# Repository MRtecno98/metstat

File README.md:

# Metstat
A fully autonomous, unattended, solar-powered, IoT weather probe with mesh networking capabilities.

<br>

## Hardware stack
| Component  | Part | Notes |
| - | - | - |
| MCU | `STM32L4A6AG` | Low power MCU with small package size, decent connectivity and hardware acceleration for crypto algorithms |
| Power Supply  | `SPV1050` | Integrated energy harvester with Max Power Point Tracking. Managing intake from solar panels and LiPo storage |
| `TODO` | `TODO` | `TODO` |

## Firmware stack
Written in C++, runs on the standard STM32 [HAL](https://www.st.com/resource/en/user_manual/um1725-description-of-stm32f4-hal-and-lowlayer-drivers-stmicroelectronics.pdf) 
using [CubeMX](https://www.st.com/en/development-tools/stm32cubemx.html) (standard runtime for STM32s).

## Technical description
`todo`

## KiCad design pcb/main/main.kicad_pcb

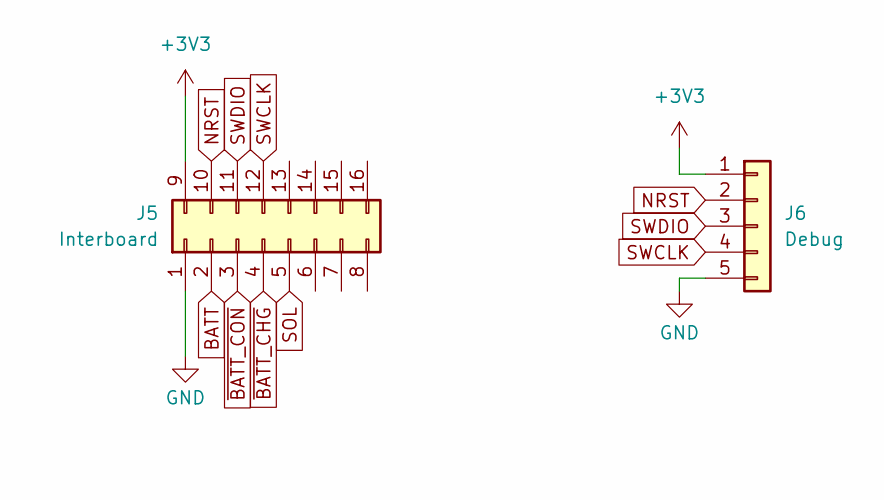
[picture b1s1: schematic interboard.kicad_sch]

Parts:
J5: Interboard; PinSocket_2x08_P2.54mm_Vertical
J6: Debug; PinHeader_1x05_P2.54mm_Horizontal

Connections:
+3V3: J5.9, J6.1; also elsewhere on the board
BATT: J5.2; also elsewhere on the board
GND: J5.1, J6.5; also elsewhere on the board
NRST: J5.10, J6.2; also elsewhere on the board
SOL: J5.5; also elsewhere on the board
SWCLK: J5.12, J6.4; also elsewhere on the board
SWDIO: J5.11, J6.3; also elsewhere on the board
~BATT_CHG: J5.4; also elsewhere on the board
~BATT_CON: J5.3; also elsewhere on the board

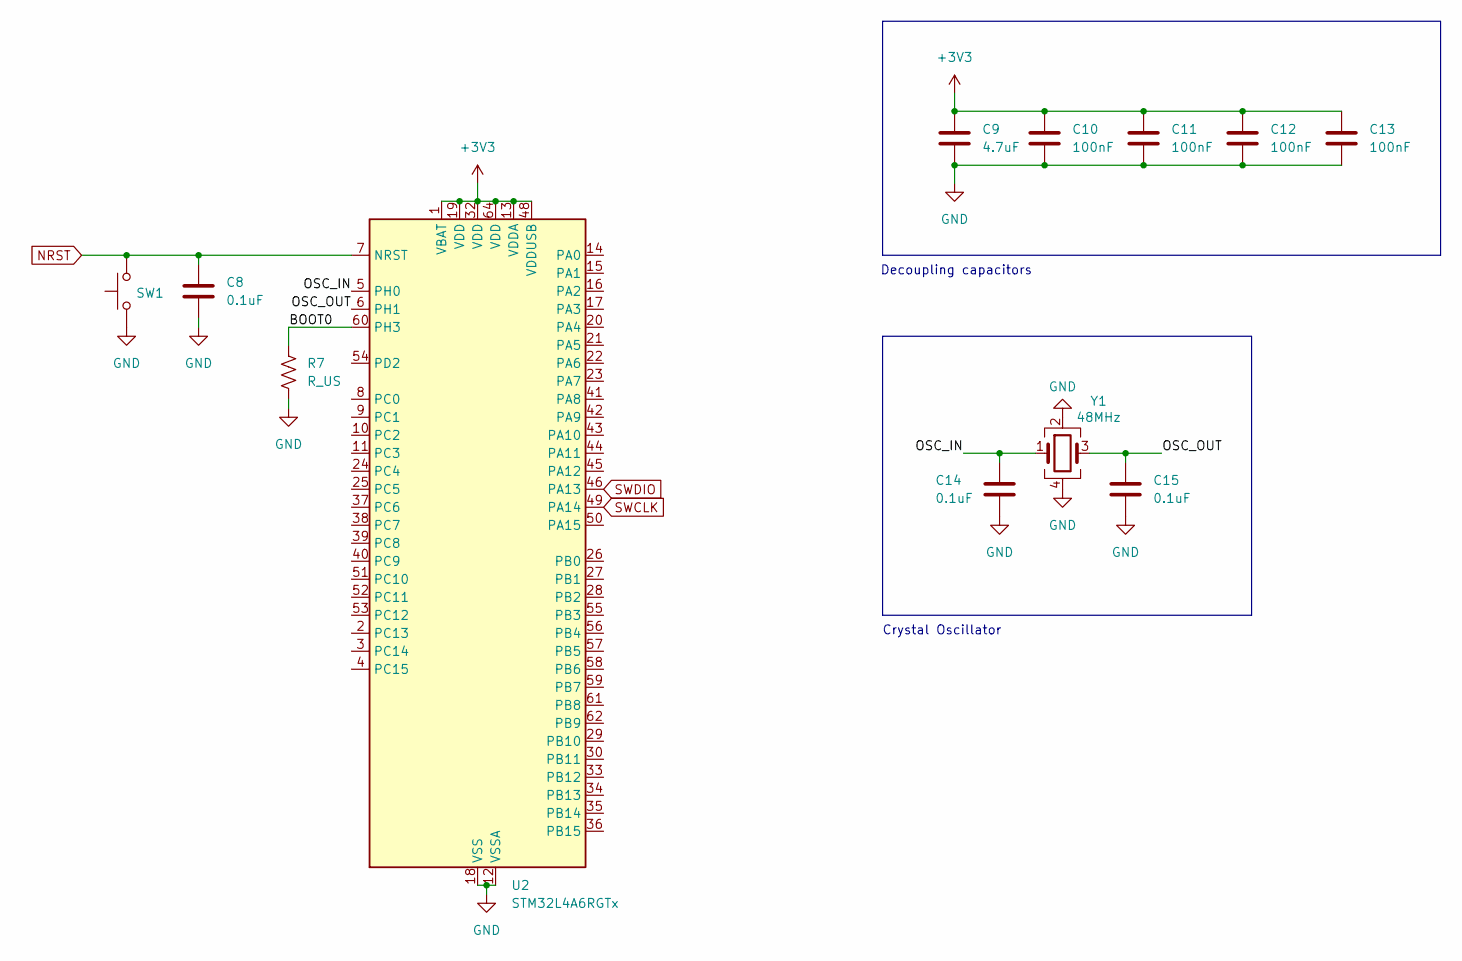
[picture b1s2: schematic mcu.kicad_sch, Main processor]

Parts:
C8, C14, C15: 0.1uF; C_0603_1608Metric_Pad1.08x0.95mm_HandSolder
C9: 4.7uF; C_0603_1608Metric_Pad1.08x0.95mm_HandSolder
C10, C11, C12, C13: 100nF; C_0603_1608Metric_Pad1.08x0.95mm_HandSolder
R7: R_US; R_0603_1608Metric_Pad0.98x0.95mm_HandSolder
SW1: SW_Push; SW_PUSH_6mm_H5mm
U2: STM32L4A6RGTx; LQFP-64_10x10mm_P0.5mm
Y1: 48MHz; Crystal_SMD_2016-4Pin_2.0x1.6mm

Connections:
+3V3: C9.1, C10.1, C11.1, C12.1, C13.1, U2.1 (VBAT), U2.13 (VDDA), U2.19 (VDD), U2.32 (VDD), U2.48 (VDDUSB), U2.64 (VDD); also elsewhere on the board
/MCU/BOOT0: R7.1, U2.60 (PH3)
/MCU/OSC_IN: C14.1, U2.5 (PH0), Y1.1
/MCU/OSC_OUT: C15.1, U2.6 (PH1), Y1.3
GND: C8.2, C9.2, C10.2, C11.2, C12.2, C13.2, C14.2, C15.2, R7.2, SW1.1, U2.12 (VSSA), U2.18 (VSS), U2.31 (VSS), U2.47 (VSS), U2.63 (VSS), Y1.2, Y1.4; also elsewhere on the board
NRST: C8.1, SW1.2, U2.7 (NRST); also elsewhere on the board
SWCLK: U2.49 (PA14); also elsewhere on the board
SWDIO: U2.46 (PA13); also elsewhere on the board

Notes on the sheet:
Crystal Oscillator
Decoupling capacitors

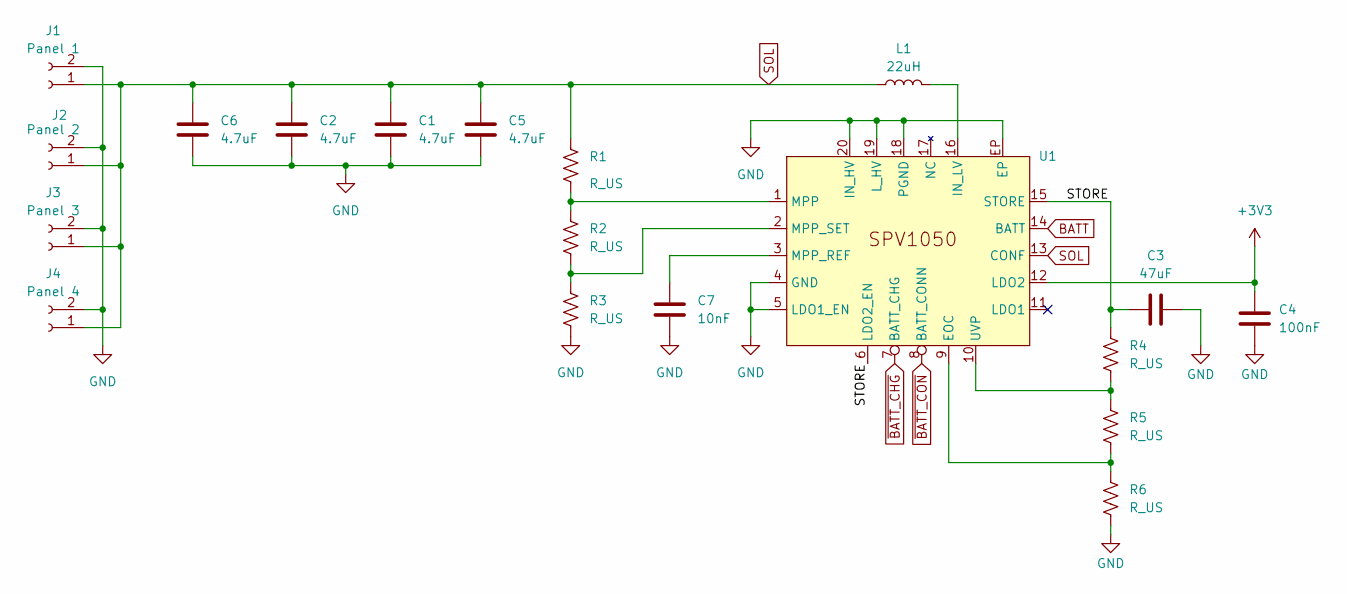
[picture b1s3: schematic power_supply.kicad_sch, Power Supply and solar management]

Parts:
C1, C2, C5, C6: 4.7uF; C_0603_1608Metric_Pad1.08x0.95mm_HandSolder
C3: 47uF; C_0603_1608Metric_Pad1.08x0.95mm_HandSolder
C4: 100nF; C_0603_1608Metric_Pad1.08x0.95mm_HandSolder
C7: 10nF; C_0603_1608Metric_Pad1.08x0.95mm_HandSolder
J1: Panel 1; Molex_PicoBlade_53261-0271_1x02-1MP_P1.25mm_Horizontal
J2: Panel 2; Molex_PicoBlade_53261-0271_1x02-1MP_P1.25mm_Horizontal
J3: Panel 3; Molex_PicoBlade_53261-0271_1x02-1MP_P1.25mm_Horizontal
J4: Panel 4; Molex_PicoBlade_53261-0271_1x02-1MP_P1.25mm_Horizontal
L1: 22uH; L_0603_1608Metric_Pad1.05x0.95mm_HandSolder
R1, R2, R3, R4, R5, R6: R_US; R_0603_1608Metric_Pad0.98x0.95mm_HandSolder
U1: SPV1050

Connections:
+3V3: C4.2, U1.12 (LDO2); also elsewhere on the board
/Power Supply/STORE: C3.2, R4.1, U1.6 (LDO2_EN), U1.15 (STORE)
BATT: U1.14 (BATT); also elsewhere on the board
GND: C1.2, C2.2, C3.1, C4.1, C5.2, C6.2, C7.2, J1.2, J2.2, J3.2, J4.2, R3.2, R6.2, U1.4 (GND), U1.5 (LDO1_EN), U1.18 (PGND), U1.19 (L_HV), U1.20 (IN_HV), U1.EP; also elsewhere on the board
unnamed: R5.2, R6.1, U1.9 (EOC)
unnamed: L1.2, U1.16 (IN_LV)
unnamed: R1.2, R2.1, U1.1 (MPP)
unnamed: C7.1, U1.3 (MPP_REF)
unnamed: R2.2, R3.1, U1.2 (MPP_SET)
unnamed: R4.2, R5.1, U1.10 (UVP)
SOL: C1.1, C2.1, C5.1, C6.1, J1.1, J2.1, J3.1, J4.1, L1.1, R1.1, U1.13 (CONF); also elsewhere on the board
~BATT_CHG: U1.7 (BATT_CHG); also elsewhere on the board
~BATT_CON: U1.8 (BATT_CONN); also elsewhere on the board

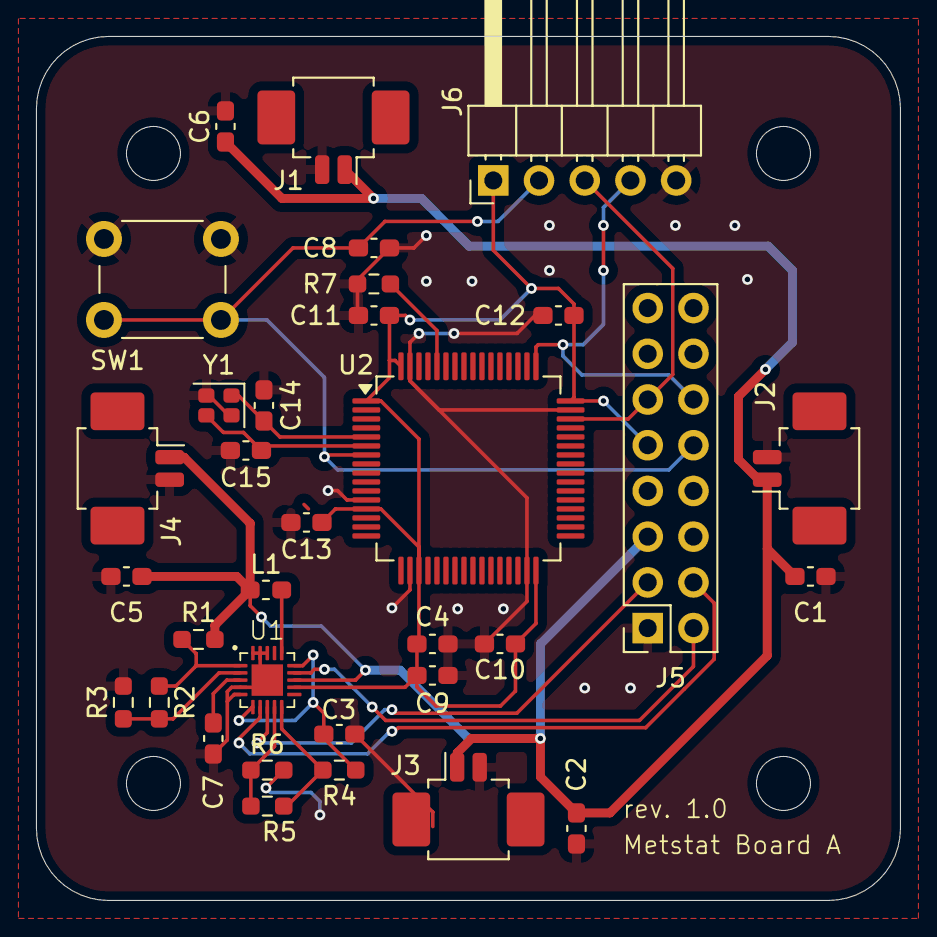
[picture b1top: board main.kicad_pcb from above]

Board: 2 copper layers, 48.0 x 48.0 mm, 33 parts (0 on the bottom side), 19 nets.

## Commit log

2025-08-19 readme: add more images
2025-08-19 readme: fix spacing
2025-08-21 add firmware
2025-09-05 update gitignore
    Now ignores temporary Solidworks files
2025-09-05 mechanical: update pcb fasteners to M3
    Now everything has the same screw size
2025-09-09 mechanical: increase mid wall thickness to 8mm
    got issue during 3d printing and also it was way too low in general
2025-09-11 Replace image link in README.md
2025-09-11 add panel models, add M3 fastener models
2025-09-11 mechanical: add m3 pcb fastener models
2025-09-11 removed gcode
2025-09-11 mechanical: update stl models
2025-09-12 add STEP files to git LFS
2025-09-12 pcb: add mounting holes, move debug connector
2025-09-12 mechanical: add main pcb to assembly
2026-01-30 add solar irradiation simulation
2026-01-31 add energy storage simulation
